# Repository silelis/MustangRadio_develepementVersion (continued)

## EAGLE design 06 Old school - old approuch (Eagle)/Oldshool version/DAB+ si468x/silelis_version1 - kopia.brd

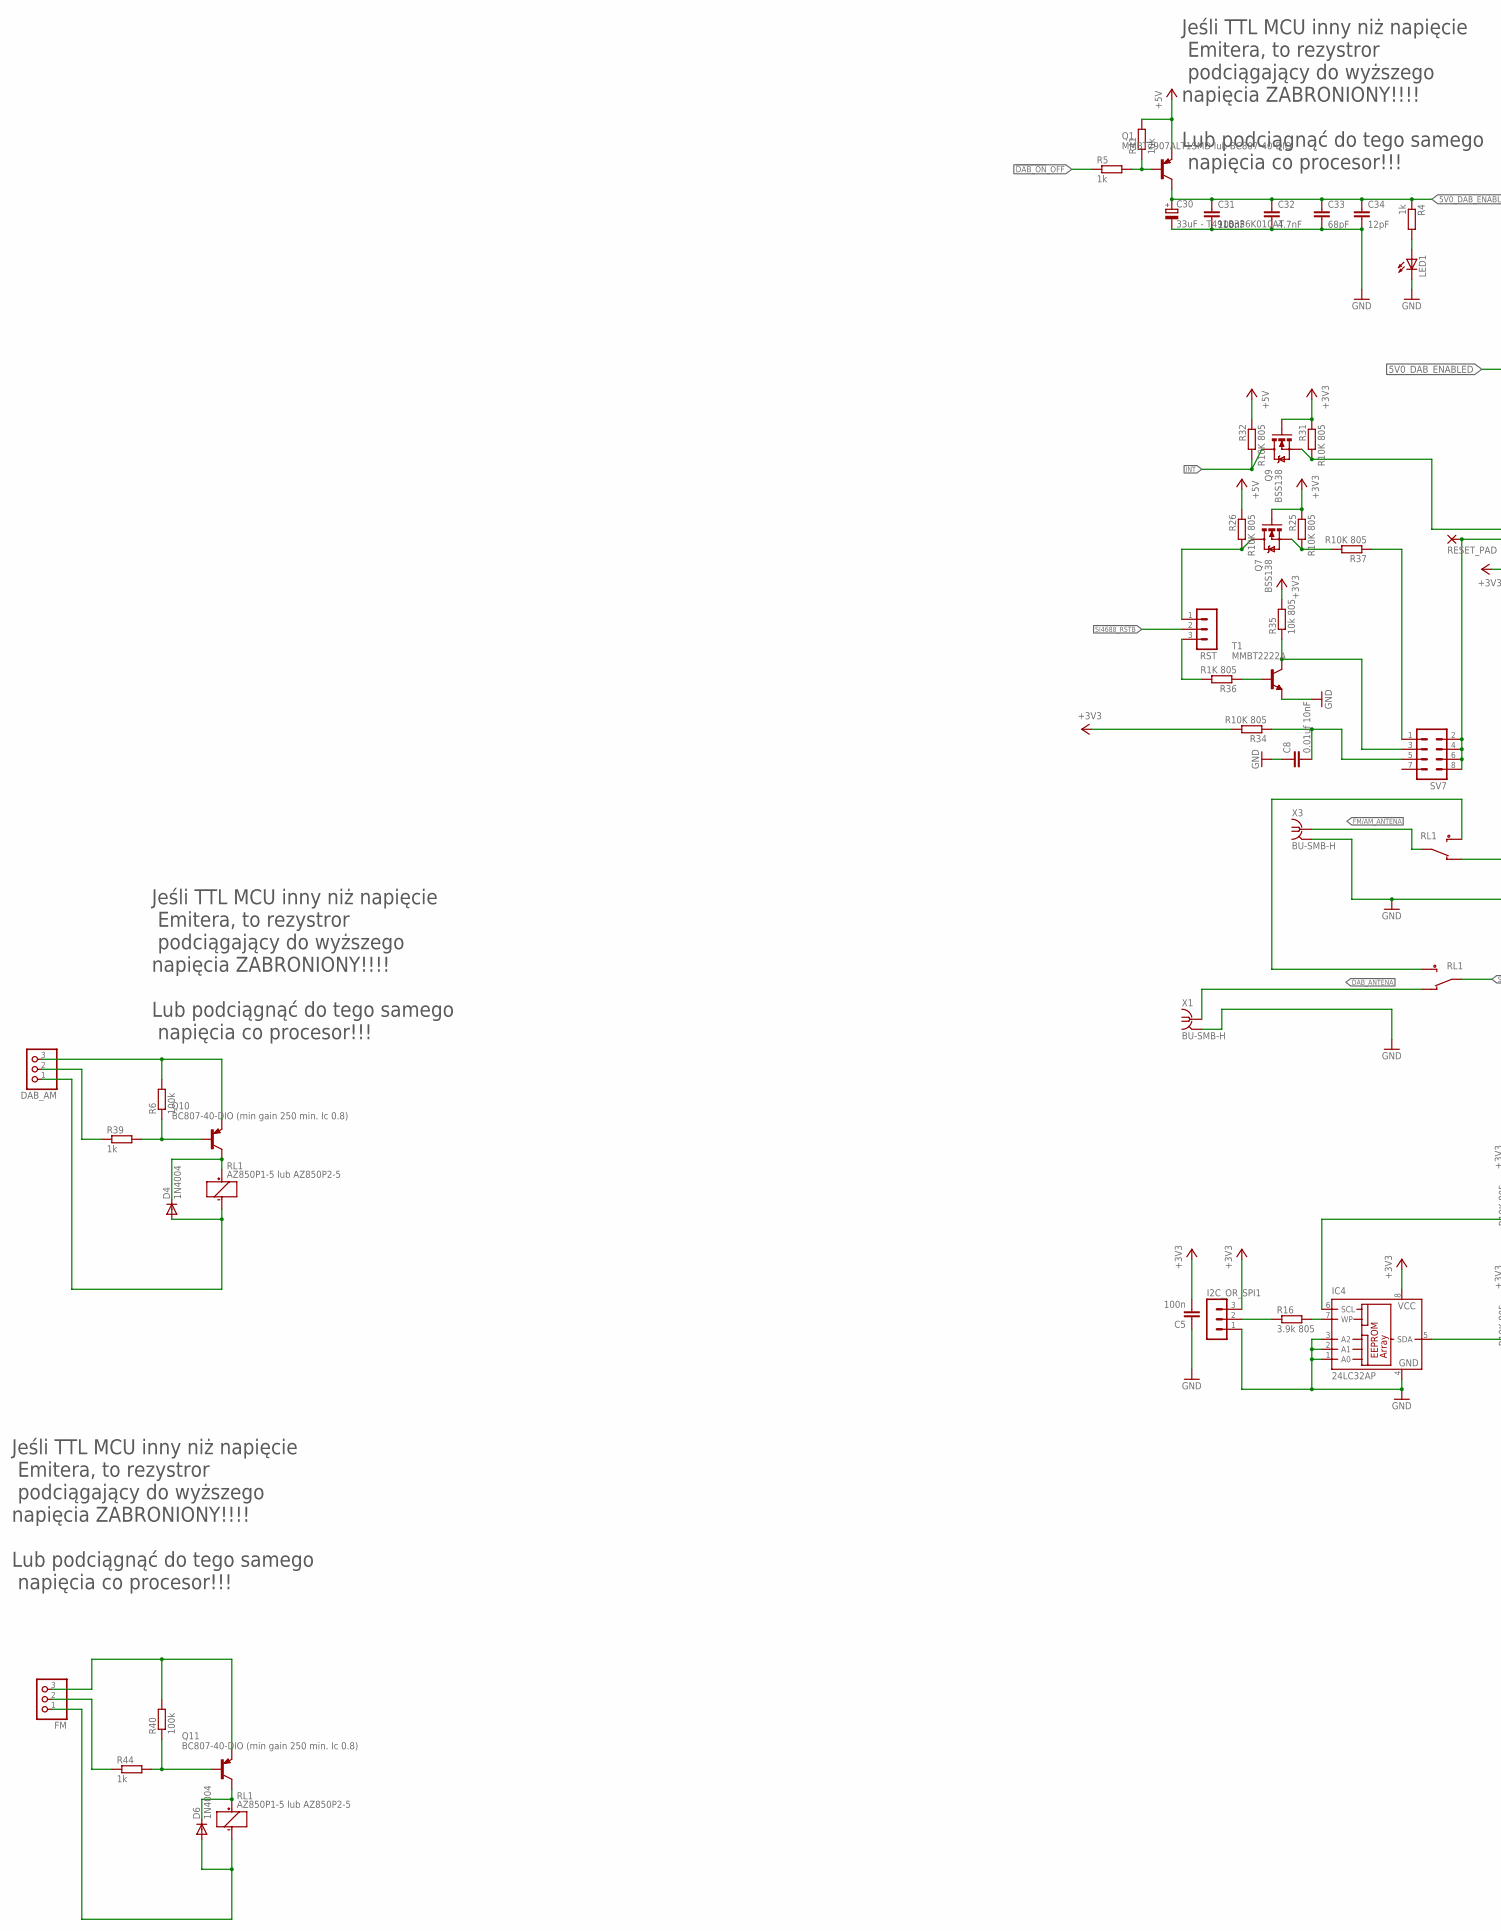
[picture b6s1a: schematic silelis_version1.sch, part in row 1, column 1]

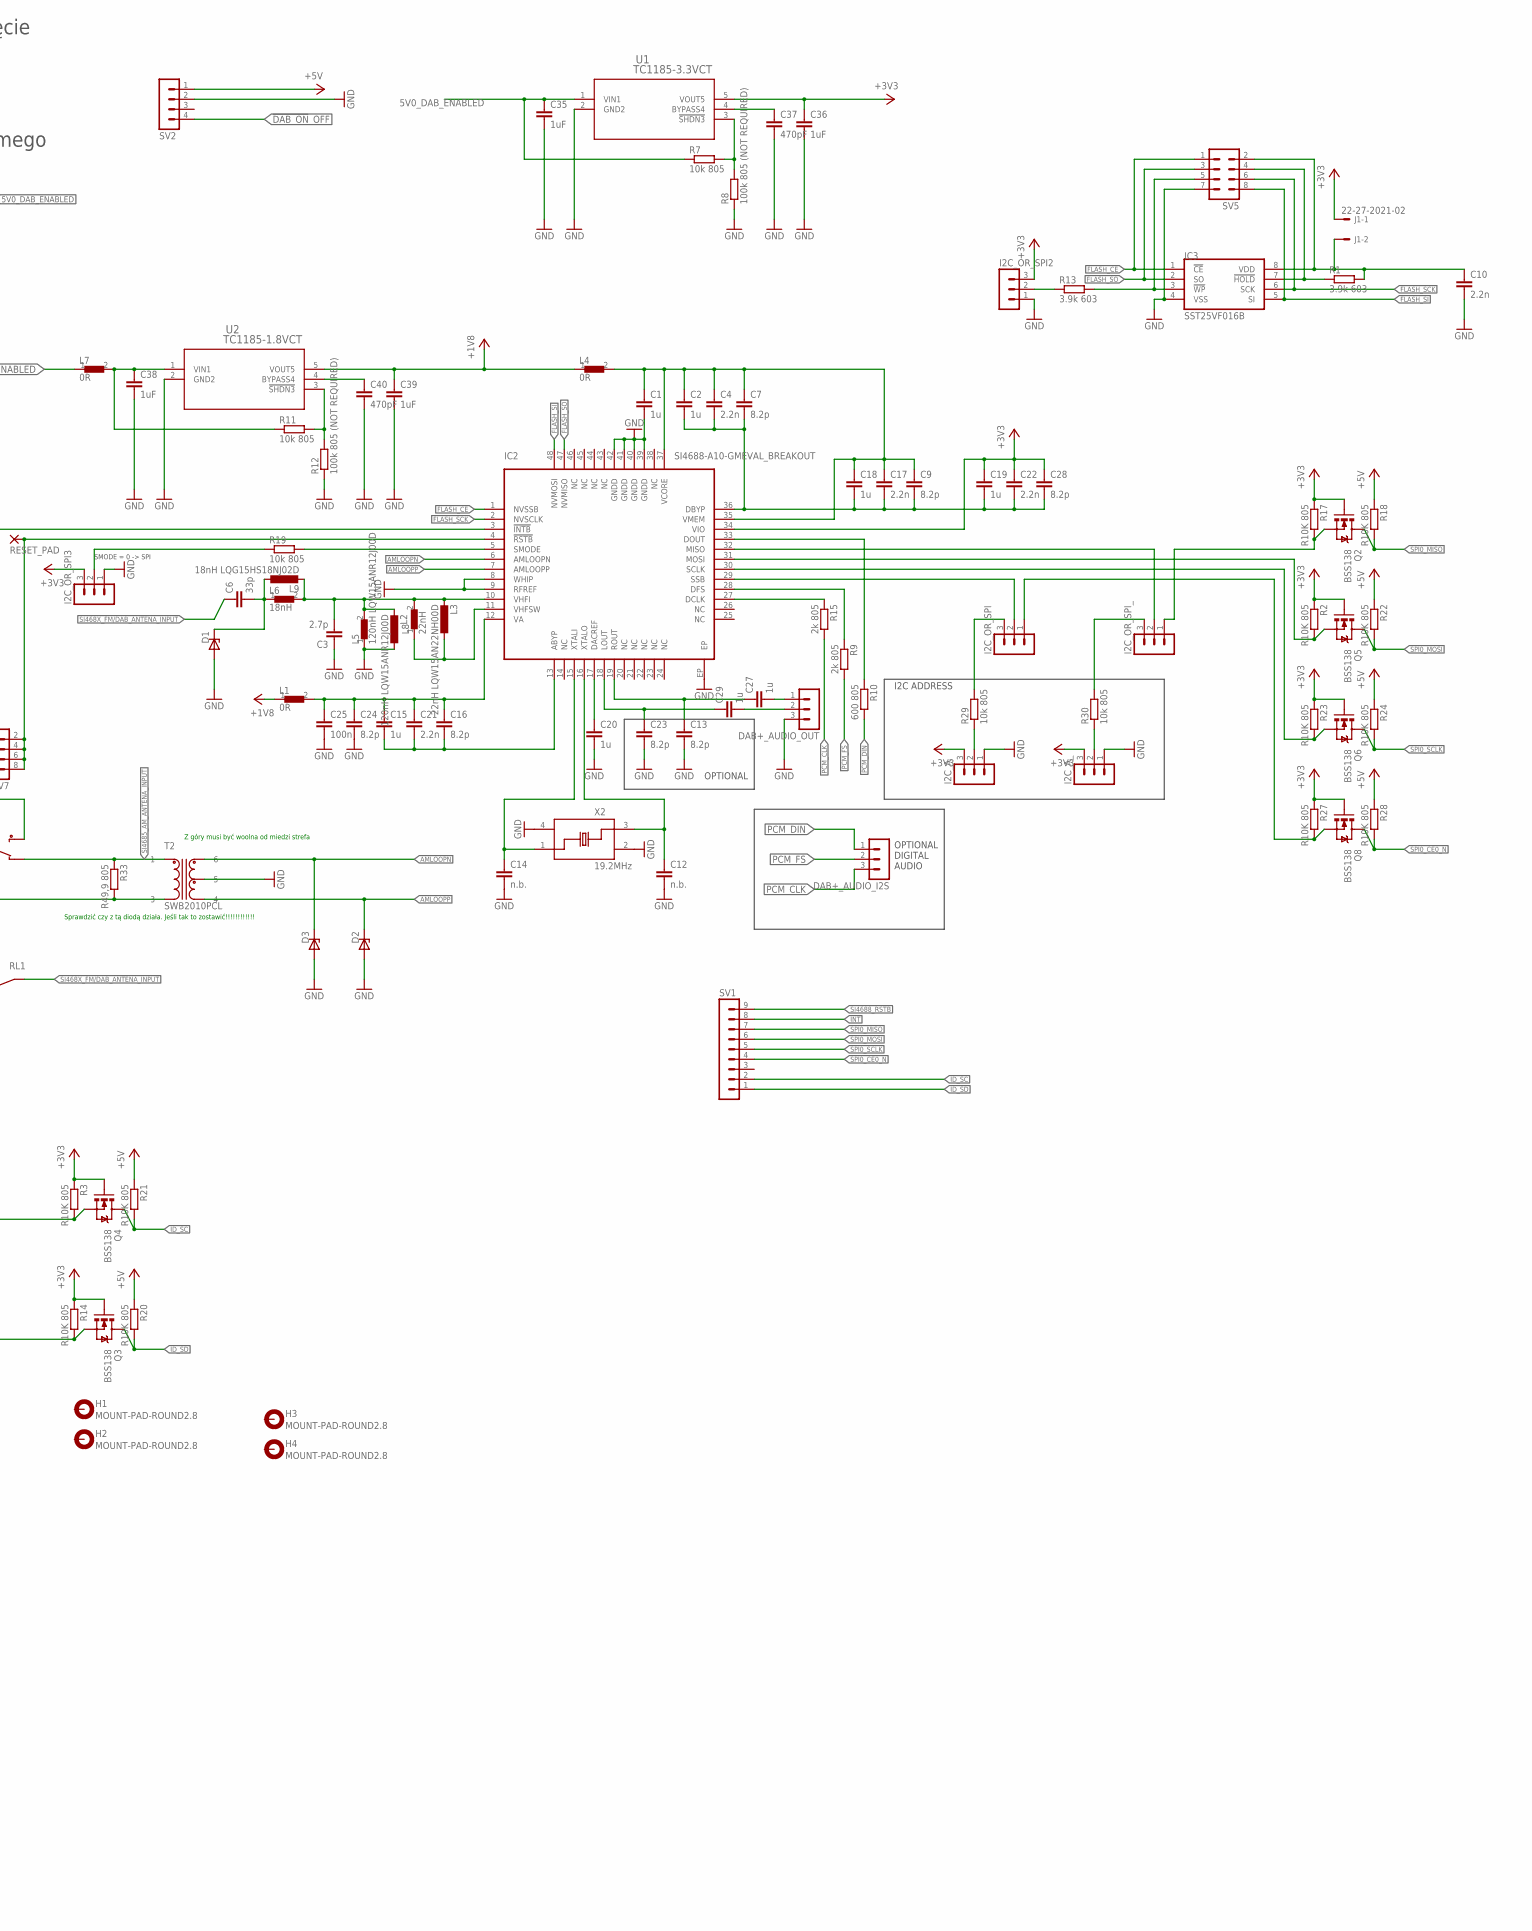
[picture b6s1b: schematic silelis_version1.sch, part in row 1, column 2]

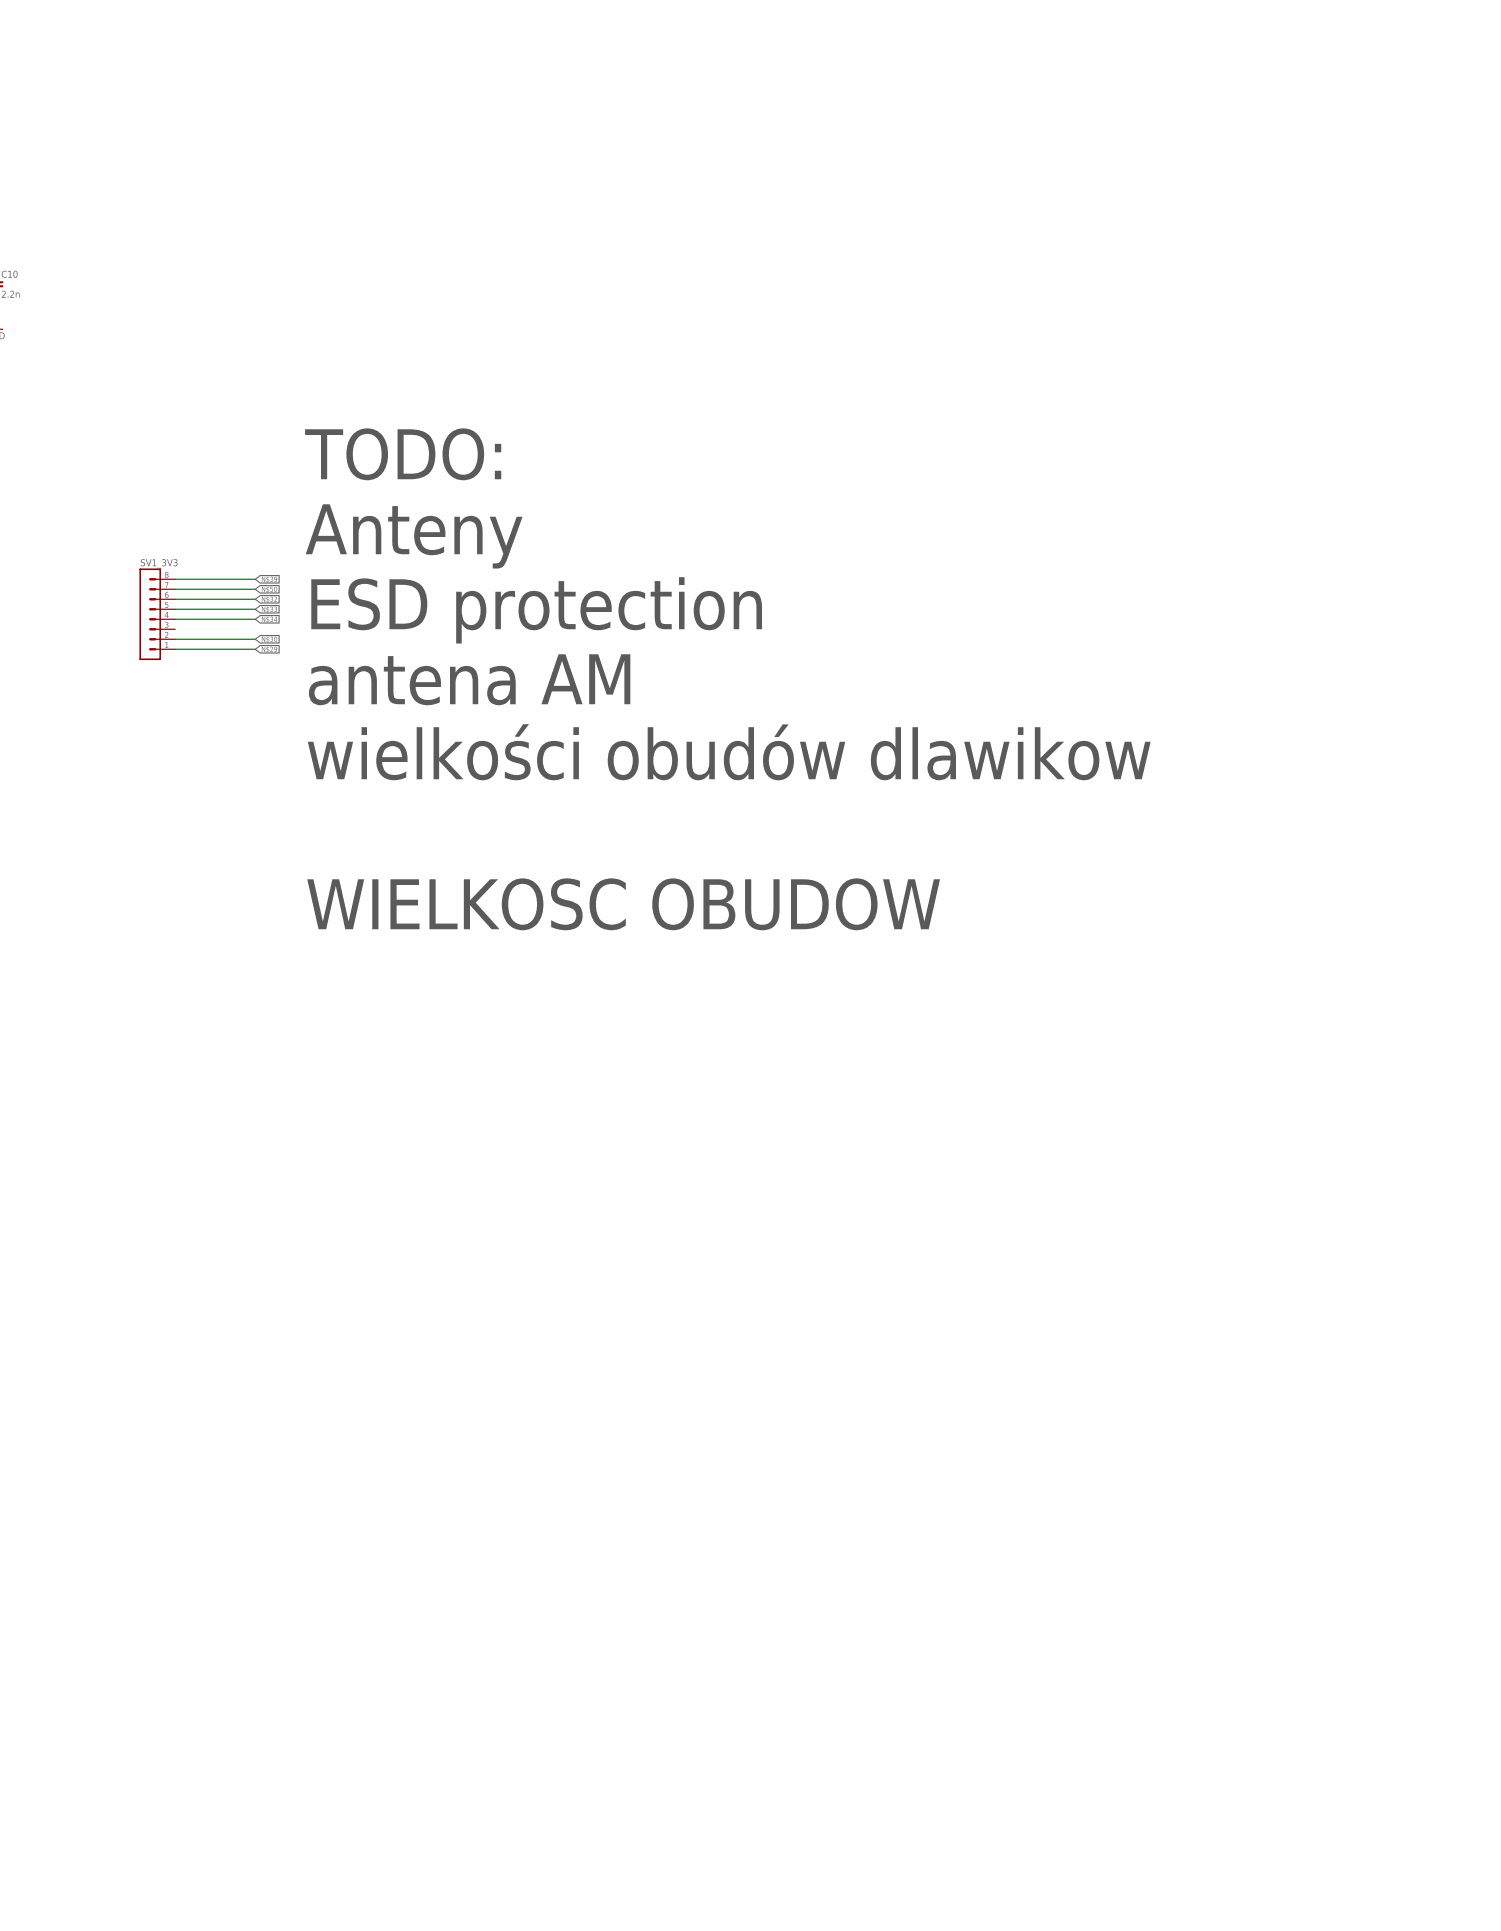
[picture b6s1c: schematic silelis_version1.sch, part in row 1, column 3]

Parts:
C1, C2, C15, C18, C19, C20, C27, C29: 1u; C0805
C3: 2.7p; C0603
C4, C10, C17, C21, C22: 2.2n; C0805
C5, C25: 100n; C0805
C6: 33p; C0603
C7, C9, C13, C16, C23, C24, C28: 8.2p; C0805
C8: 0.01uf 10nF; C0805
C12, C14: n.b.; C0805
C30: 33uF - T491B336K010AT; SMC_B; PARTNUM TAJB336K010R
C31: 100nF; C0805
C32: 4.7nF; C0805
C33: 68pF; C0805
C34: 12pF; C0603K
C35, C36, C38, C39: 1uF; C0805
C37, C40: 470pF; C0805
D1, D2, D3: ESD9L5.0; SOD923
D4, D6: 1N4004; DO41-10
DAB+_AUDIO_I2S: MA03-1
DAB+_AUDIO_OUT: MA03-1
DAB_AM: PINHD-1X03_2.54-SMD; 1X03SMD
FM: PINHD-1X03_2.54-SMD; 1X03SMD
H1, H2, H3, H4: MOUNT-PAD-ROUND2.8; 2,8-PAD
I2C_A, I2C_A_, I2C_OR_SPI, I2C_OR_SPI1, I2C_OR_SPI2, I2C_OR_SPI3, I2C_OR_SPI_: MA03-1
IC2: SI4688-A10-GMEVAL_BREAKOUT; QFN48-BREAKOUT
IC3: SST25VF016B; SOIC-8
IC4: 24LC32AP; DIL8
J1: 22-27-2021-02; 6410-02
L1, L4, L7: 0R; R0805
L2: 120nH LQW15ANR12J00D; SMD0402
L3: 22nH LQW15AN22NH00D; SMD0402
L5: 120nH LQW15ANR12J00D; R0805
L6: 18nH; R0805
L8: 22nH; R0805
L9: 18nH LQG15HS18NJ02D; SMD0402
LED1: LED3MM
Q1: MMBT2907ALT1SMD lub BC807-40-DIO; SOT23-BEC
Q2, Q3, Q4, Q5, Q6, Q7, Q8, Q9: BSS138; SOT23-3
Q10, Q11: BC807-40-DIO (min gain 250 min. Ic 0.8); SOT23-BEC
R1, R13: 3.9k 603; R0603
R2, R3, R14, R17, R18, R20, R21, R22, R23, R24, R25, R26, R27, R28, R31, R32, R34, R37: R10K 805; R0805
R4, R5, R39, R44: 1k; M0805
R6, R40: 100k; M0805
R7, R11, R19, R29, R30, R35: 10k 805; M0805
R8, R12: 100k 805 (NOT REQUIRED); M0805
R9, R15: 2k 805; M0805
R10: 600 805; M0805
R16: 3.9k 805; R0805
R33: R49,9 805; R0805
R36: R1K 805; R0805
R41: 10k; M0805
RESET_PAD: SMD2; SMD1,27-2,54
RL1: AZ850P1-5 lub AZ850P2-5; AZ850-2C
RST: MA03-1
SV1: MA09-1
SV1_3V3: MA08-1
SV2: MA04-1
SV5, SV7: MA04-2
T1: MMBT2222A; SOT23-BEC
T2: SWB2010PCL; COILCRAFT-SWBXXXX-PCL
U1: TC1185-3.3VCT; SOT-23-5_MC-M
U2: TC1185-1.8VCT; SOT-23-5_MC-M
X1, X3: BU-SMB-H
X2: 19.2MHz; XTAL_3.2X2.5

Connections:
5V0_DAB_ENABLED: C30.+, C31.1, C32.1, C33.1, C34.1, C35.1, L7.1, Q1.C, R4.1, R7.1, U1.1 (VIN1)
!DAB_ON!_OFF: R5.1, SV2.4
+1V8: C39.1, L1.1, L4.1, U2.5 (VOUT5)
+3V3: C5.2, C19.1, C22.1, C28.1, C36.1, I2C_A.3, I2C_A_.3, I2C_OR_SPI1.3, I2C_OR_SPI2.3, I2C_OR_SPI3.3, IC2.34 (VIO), IC4.8 (VCC), J1.1, Q2.1 (G), Q3.1 (G), Q4.1 (G), Q5.1 (G), Q6.1 (G), Q7.1 (G), Q8.1 (G), Q9.1 (G), R2.1, R3.1, R14.1, R17.1, R23.1, R25.1, R27.1, R31.1, R34.2, R35.2, U1.5 (VOUT5)
+5V: Q1.E, R18.1, R20.1, R21.1, R22.1, R24.1, R26.1, R28.1, R32.1, R41.2, SV2.1
AMLOOPN: D3.K (C), IC2.6 (AMLOOPN), T2.P$6 (6)
AMLOOPP: D2.K (C), IC2.7 (AMLOOPP), T2.P$4 (4)
DAB/AM_POSITION: DAB_AM.2, R39.1; also elsewhere on the board
DAB_ANTENA: RL1.P$9 (4), X1.1
FLASH_CE: IC2.1 (NVSSB), IC3.1 (!CE), SV5.1
FLASH_SCK: IC2.2 (NVSCLK), IC3.6 (SCK), SV5.6
FLASH_SI: IC2.48 (NVMOSI), IC3.5 (SI), SV5.8
FLASH_SO: IC2.47 (NVMISO), IC3.2 (SO), SV5.3
FM/AM_ANTENA: RL1.P$3 (5), X3.1
FM/AM_ANTENA_TO_SI468X_FM/DAB_ANTENA_INPUT: RL1.P$4 (6), RL1.P$7 (6)
FM_POSITION: FM.2, R44.1; also elsewhere on the board
GND: C1.2, C3.1, C5.1, C8.1, C10.2, C12.2, C13.2, C14.2, C20.2, C23.2, C24.2, C25.2, C30.-, C31.2, C32.2, C33.2, C34.2, C35.2, C36.2, C37.2, C38.2, C39.2, C40.2, D1.A, D2.A, D3.A, DAB+_AUDIO_OUT.3, I2C_A.1, I2C_A_.1, I2C_OR_SPI1.1, I2C_OR_SPI2.1, I2C_OR_SPI3.1, IC2.8 (WHIP), IC2.9 (RFREF), IC2.39 (GNDD), IC2.40 (GNDD), IC2.41 (GNDD), IC2.42 (GNDD), IC2.EP, IC3.4 (VSS), IC4.1 (A0), IC4.2 (A1), IC4.3 (A2), IC4.4 (GND), L2.1, L5.1, LED1.K (C), R8.1, R12.1, R33.2, SV2.2, SV5.7, T1.E, T2.P$3 (3), T2.P$5 (5), U1.2 (GND2), U2.2 (GND2), X1.2, X1.3 (2), X1.4 (2), X1.5 (2), X2.2 (GND), X2.4 (GND), X3.2, X3.3 (2), X3.4 (2), X3.5 (2)
ID_SC: Q4.3 (D), R21.2, SV1.2
ID_SD: Q3.3 (D), R20.2, SV1.1
INT: Q9.3 (D), R32.2, SV1.8
unnamed: C3.2, IC2.10 (VHFI), L2.2, L3.2, L5.2, L6.2, L8.2, L9.2
unnamed: IC2.11 (VHFSW), L3.1, L8.1
unnamed: C15.2, C16.2, C21.2, IC2.13 (ABYP)
unnamed: C2.2, C4.2, C7.2, C9.2, C17.2, C18.2, C19.2, C22.2, C28.2, IC2.36 (DBYP)
unnamed: C14.1, IC2.15 (XTALI), X2.1
unnamed: C12.1, IC2.16 (XTALO), X2.3
unnamed: C20.1, IC2.17 (DACREF)
unnamed: IC2.4 (!RSTB!), RESET_PAD.1, SV7.2, SV7.4, SV7.6, SV7.8
unnamed: I2C_OR_SPI2.2, R13.1
unnamed: C38.1, L7.2, R11.1, U2.1 (VIN1)
unnamed: C15.1, C16.1, C21.1, C24.1, C25.1, IC2.12 (VA), L1.2
unnamed 31: D4.A, DAB_AM.1, RL1.P$5 (-); also elsewhere on the board
unnamed: C1.1, C2.1, C4.1, C7.1, C9.1, C17.1, C18.1, IC2.35 (VMEM), IC2.37 (VCORE), L4.2
unnamed: IC2.28 (DFS), R9.1
unnamed: IC2.33 (DOUT), R10.1
unnamed: IC4.7 (WP), R16.2
unnamed: LED1.A, R4.2
unnamed: Q1.B, R5.2, R41.1
unnamed: C37.1, U1.4 (BYPASS4)
unnamed: R7.2, R8.2, U1.3 (!SHDN3)
unnamed: IC3.7 (!HOLD), R1.1, SV5.4
unnamed: IC2.27 (DCLK), R15.1
unnamed: C40.1, U2.4 (BYPASS4)
unnamed: R11.2, R12.2, U2.3 (!SHDN3)
unnamed: I2C_OR_SPI3.2, R19.1
unnamed: IC2.5 (SMODE), R19.2
unnamed: I2C_OR_SPI1.2, R16.1
unnamed: IC4.5 (SDA), Q3.2 (S), R14.2, SV1_3V3.1
unnamed: IC4.6 (SCL), Q4.2 (S), R3.2, SV1_3V3.2
unnamed: I2C_OR_SPI_.2, IC2.32 (MISO)
unnamed: IC2.31 (MOSI), Q5.2 (S), R2.2, SV1_3V3.6
unnamed: IC2.30 (SCLK), Q6.2 (S), R23.2, SV1_3V3.5
unnamed: I2C_OR_SPI.1, Q8.2 (S), R27.2, SV1_3V3.4
unnamed: I2C_A.2, R29.1
unnamed: I2C_A_.2, R30.1
unnamed: I2C_OR_SPI.3, R29.2
unnamed: I2C_OR_SPI_.3, R30.2
unnamed: IC2.3 (!INTB!), Q9.2 (S), R31.2, SV1_3V3.8
unnamed: R35.1, SV7.3, T1.C
unnamed: C10.1, IC3.8 (VDD), J1.2, R1.2, SV5.2
unnamed: IC3.3 (!WP), R13.2, SV5.5
unnamed: C27.2, DAB+_AUDIO_OUT.1
unnamed: C29.2, DAB+_AUDIO_OUT.2
unnamed: I2C_OR_SPI.2, IC2.29 (SSB)
unnamed: I2C_OR_SPI_.1, Q2.2 (S), R17.2, SV1_3V3.7
unnamed: R36.2, RST.3
unnamed: C8.2, R34.1, SV7.5
unnamed: R36.1, T1.B
unnamed: Q7.2 (S), R25.2, R37.2
unnamed: Q7.3 (D), R26.2, RST.1
unnamed: R37.1, SV7.1
unnamed: Q10.B, R6.1, R39.2
unnamed 72: DAB_AM.3, Q10.E, R6.2; also elsewhere on the board
unnamed: D4.C, Q10.C, RL1.P$1 (+)
unnamed: Q11.B, R40.1, R44.2
unnamed 75: FM.3, Q11.E, R40.2; also elsewhere on the board
unnamed 76: D6.A, FM.1, RL1.P$6 (-); also elsewhere on the board
unnamed: D6.C, Q11.C, RL1.P$10 (+)
PCM_CLK: DAB+_AUDIO_I2S.3, R15.2
PCM_DIN: DAB+_AUDIO_I2S.1, R10.2
PCM_FS: DAB+_AUDIO_I2S.2, R9.2
SI4685_AM_ANTENA_INPUT: R33.1, RL1.P$2 (4), T2.P$1 (1)
SI4688_LOUT: C23.1, C29.1, IC2.18 (LOUT)
SI4688_ROUT: C13.1, C27.1, IC2.19 (ROUT)
SI4688_RSTB: RST.2, SV1.9
SPI0_CE0_N: Q8.3 (D), R28.2, SV1.4
SPI0_MISO: Q2.3 (D), R18.2, SV1.7
SPI0_MOSI: Q5.3 (D), R22.2, SV1.6
SPI0_SCLK: Q6.3 (D), R24.2, SV1.5

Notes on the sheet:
SMODE = 0 -> SPI
OPTIONAL DIGITAL AUDIO
TODO: Anteny ESD protection antena AM wielkości obudów dlawikow WIELKOSC OBUDOW
I2C ADDRESS
OPTIONAL
Jeśli TTL MCU inny niż napięcie Emitera, to rezystror podciągający do wyższego napięcia ZABRONIONY!!!! Lub podciągnąć do tego samego napięcia co procesor!!!
Sprawdzić czy z tą diodą działa. Jeśli tak to zostawić!!!!!!!!!!!!
Z góry musi być woolna od miedzi strefa

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
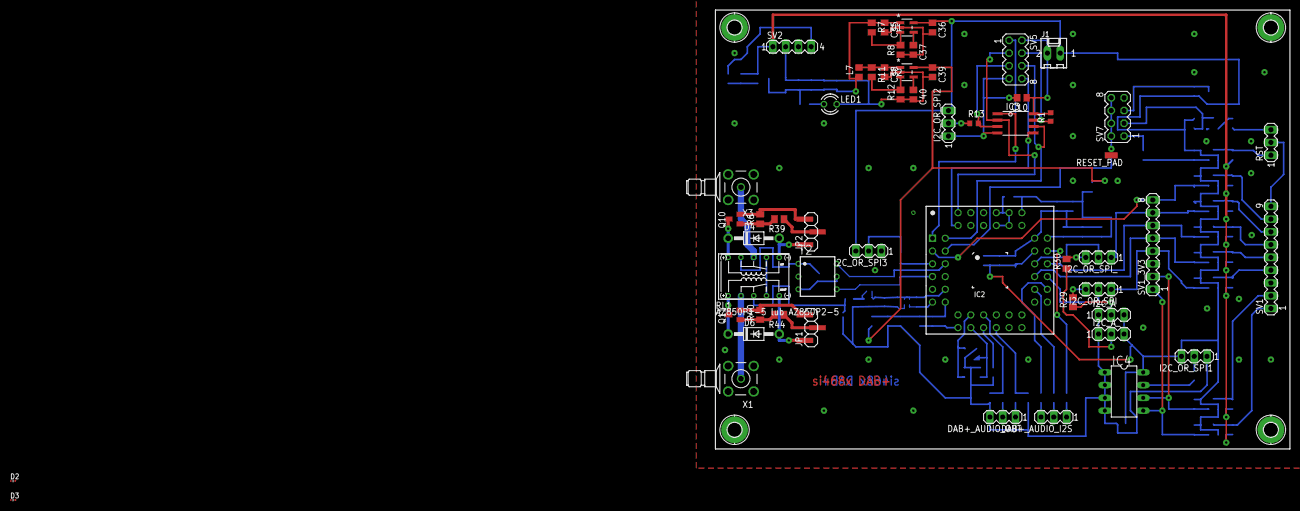
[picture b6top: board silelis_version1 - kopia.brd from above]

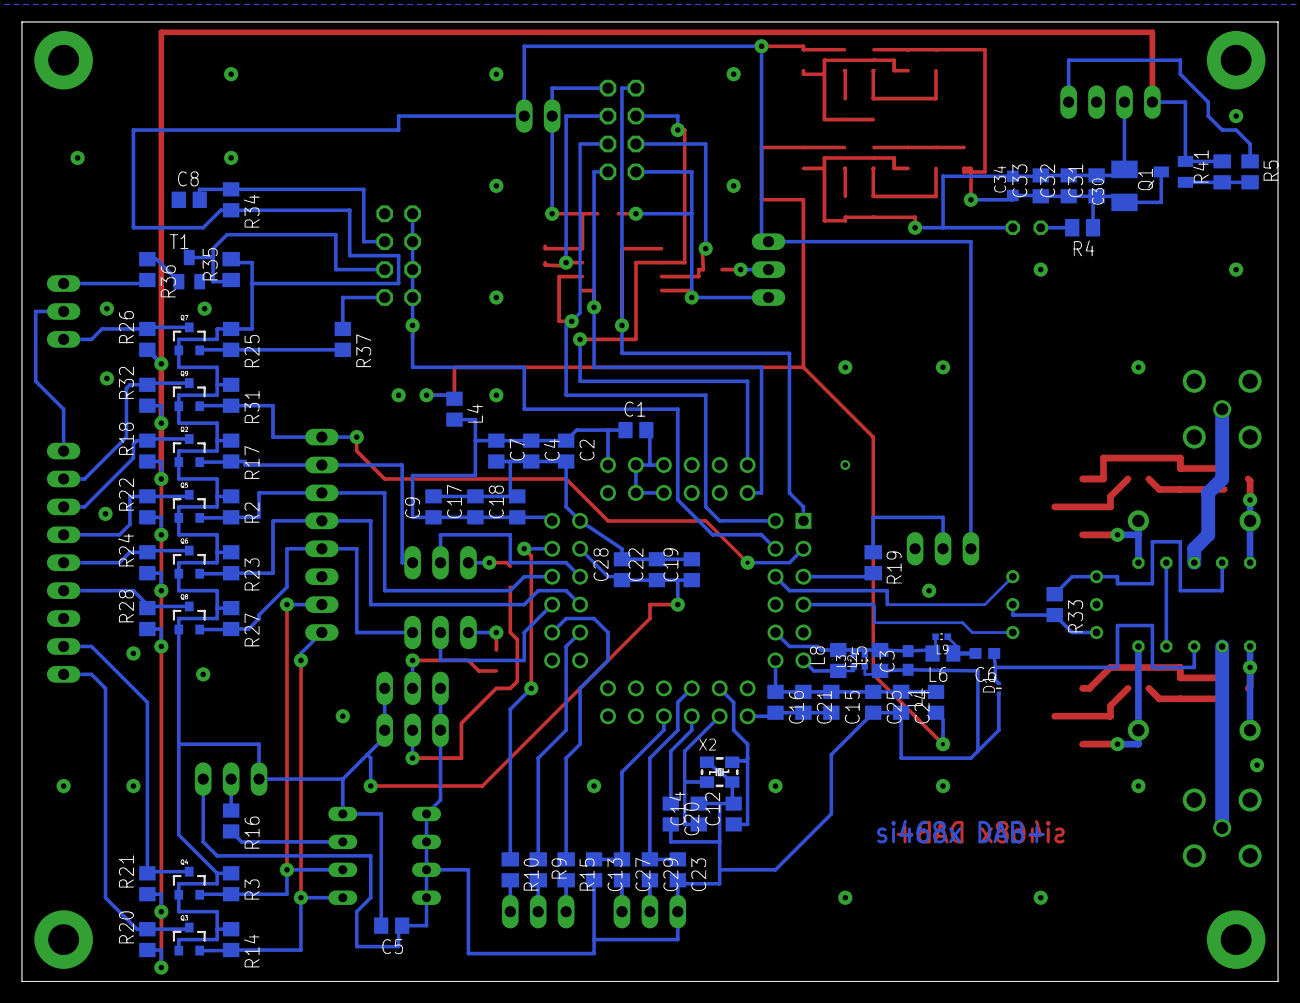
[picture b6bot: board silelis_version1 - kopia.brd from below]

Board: 2 copper layers, 114.3 x 87.3 mm, 139 parts (80 on the bottom side), 91 nets.

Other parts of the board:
JP1, JP2: 1X03SMD

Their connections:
DAB/AM_POSITION: JP2.2; also elsewhere on the board
FM_POSITION: JP1.2; also elsewhere on the board
unnamed 31: JP2.1; also elsewhere on the board
unnamed 72: JP2.3; also elsewhere on the board
unnamed 75: JP1.3; also elsewhere on the board
unnamed 76: JP1.1; also elsewhere on the board

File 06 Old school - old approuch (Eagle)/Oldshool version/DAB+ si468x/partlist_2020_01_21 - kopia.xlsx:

Partl | ist
Expor | ted | from silelis_version1.sch at 21.01.2020 11:50
EAGLE | Ve | rsion 7.6.0 Copyright (c) 1988-2016 CadSoft
Assem | bly | variant:
Part |  | Value | ilość | Device | Package | Library | Sheet
 |  |  |  |  |  |  |  |  | Mouser |  | TME
 |  |  |  |  |  |  |  |  | Cena | link | Cena | Link
IC2 |  | SI4688-A10-GMEVAL_BREAKOUT |  | SI4688-A10-GMEVAL_B | REAKOUT QFN48-BREAKOUT | SI4688-A10- | GM 1 |  | 60.17 | SI4689-A10-GM
IC3 |  | SST25VF016B |  | SST25VF016B | SOIC-8 | sst25 | 1 |  | 5.58 | SST25VF016B-50-4I-S2AF | 5.16 | SST25VF016B-50-4I-S2AF
T2 |  | SWB2010PCL |  | SWB2010PCL | COILCRAFT-SWBXXXX-PCL | CoilCraft | 1 |  | 13.12 | SWB2010PCL
U2 |  | TC1185-1.8VCT |  | TC1185-X.XXCT713SOT | -23-5_MC-M SOT-23-5_MC-M | TC1185 | 1 |  | 1.45 | TC1185-1.8VCT | 1.3466 | TC1185-1.8VCT
U1 |  | TC1185-3.3VCT |  | TC1185-X.XXCT713SOT | -23-5_MC-M SOT-23-5_MC-M | TC1185 | 1 |  | 1.45 | TC1185-3.3VCT | 1.4467000000000001 | TC1185-3.3VCT
X1-DA | B_A | NT SMA_LP_1.57MM |  | SMA_LP_1.57MM | SMA_LP_1.57MM | con_sma | 1 |  |  |  | 11.89 | SMB1252B13G50
 |  |  |  |  |  |  |  |  |  |  | 50.53 | A00030 | SMB1252B13G50 lub | antena: | A00030
 |  |  |  |  |  |  |  |  |  |  | 3.66 | ZRS-AA-4
X2-FM | _AM | _ANT |  | MTA02-156 | 1X2MTA | con-amp | 1 |  | 9.94 | Amphenol RF2FA1-NCRP-PCB-6 / MOLEX 73403-5112 / DELOCK 89773 FAKRA B |  | Amphenol RF2FA1-NCRP-PCB-6 / MOLEX 73403-5112 / DELOCK 89773 FAKRA B
 |  |  |  |  |  |  |  |  |  |  | 8.9600000000000009 | ZRS-FAKRA-DIN
 |  |  |  |  |  |  |  |  |  |  |  |  | CAR-GNANT lub CAR-006 lub (ZRS-AA-4 + Amphenol RF2FA1-NCRP-PCB-6 / MOLEX 73403-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
IC4 |  | 24LC32AP |  | 24LC32AP | DIL8 | microchip | 1 | czy nie potrzebny większy |  |  |  |  | 24LC512-I/P
RL1 |  | AZ850P2-5 | 1 | AZ850P2-5 | AZ850-2C | relay_silel | is 1 |  | 13.25 | 769-TQ2-5V | 12.01 | AZ850P2-5
X2 |  | 19.2MHz |  | XTAL_3.2X2.5 | XTAL_3.2X2.5 | generisch | 1 |  | 4.08 | ABM8-19.200MHZ-10-1-U-T | 9.5225600000000004 | I747-2P3-19.2000M (OSTATECZNIE??) | ABM8-19.200MHZ-10-1-U-T
R6 |  | 100k | 4 | R-EU_M0805 | M0805 | rcl | 1
L1 |  | 0R | 3 | FERRITR0805 | R0805 | ferrit_bear | 1 | mam 1R
R7 |  | 10k 805 | 25 | R-EU_M0805 | M0805 | rcl | 1
R4 |  | 1k | 5 | R-EU_M0805 | M0805 | rcl | 1
R9 |  | 2k 805 | 5 | R-EU_M0805 | M0805 | rcl | 1
R1 |  | 3.9k 805 | 3 | R-EU_M0805 | M0805 | rcl | 1 | mam 3.9k 1206 | 0.51 | 279-CPF0603B3K9E1 | 0.35199999999999998 | ERA3AEB392V
R44 |  | 4.7k | 1 | R-EU_M0805 | M0805 | rcl | 1
R10 |  | 600805 |  | R-EU_M0805 | M0805 | rcl | 1 | mam 680
D4 |  | 1N4004 |  | 1N4004 | DO41-10 | adafruit | 1
D6 |  | 1N4004 |  | 1N4004 | DO41-10 | adafruit | 1
L5 |  | 120nH |  | FERRITR0805 | R0805 | ferrit_bear | 1 |  | 0.70599999999999996 | LQW15ANR12J00D | 0.52447999999999995 | LQW18ANR12G00D | LQW15ANR12J00D | wziąć też jakieś 604
L6 |  | 18nH |  | FERRITR0805 | R0805 | ferrit_bear | 1 |  | 0.39200000000000002 | LQG15HS18NJ02D | 0.39484000000000002 | LQG18HN18NJ00D | LQG15HS18NJ02D | wziąć też jakieś 604
L8 |  | 22nH |  | FERRITR0805 | R0805 | ferrit_bear | 1 |  | 0.746 | LQW15AN22NH00D | 0.39493 | LQG18HN22NJ00D | LQW15AN22NH00D | wziąć też jakieś 604
C40 |  | 470pF | 2 | C-EUC0805 | C0805 | resistor | 1
C33 |  | 68pF | 1 | C-EUC0805 | C0805 | resistor | 1
C7 |  | 8.2p | 7 | C-EUC0805 | C0805 | resistor | 1
C6 |  | 33p |  | C-EUC0805 | C0805 | resistor | 1 |  | 0.23499999999999999 | 80-C0603C330K5HAUTO | 0.45008999999999999 | C0603C330J1GACTU
C3 |  | 2.7p |  | C-EUC0805 | C0805 | resistor | 1 |  | 0.39200000000000002 | 603-C0603CRNPO9BN2R7 (za 1) | 8.2369999999999999E-2 | CL10C2R7CB8NNNC (za 100)
C34 |  | 12pF |  | C-EUC0603K | C0603K | resistor | 1
C4 |  | 2.2n | 5 | C-EUC0805 | C0805 | resistor | 1
C8 |  | 0.01uf 10n |  | C-EUC0805 | C0805 | rcl | 1
C32 |  | 4.7nF | 1 | C-EUC0805 | C0805 | resistor | 1
C5 |  | 100n | 3 | C-EUC0805 | C0805 | resistor | 1
C1 |  | 1u | 12 | C-EUC0805 | C0805 | resistor | 1
C30 |  | 33uF - T491B336K010AT |  | CPOL-EUSMCB | SMC_B | resistor | 1
C12 |  | n.b. |  | C-EUC0805 | C0805 | resistor | 1
C14 |  | n.b. |  | C-EUC0805 | C0805 | resistor | 1
Q10 |  | BC807-40-DIO (min gain 250 min. Ic 0.8) | 2 | MMBT2907ALT1SMD | SOT23-BEC | transistor- | pnp 1 | PNP |  |  |  |  | MMBT5401
Q2 |  | BSS138 | 8 | MOSFET-NCHANNELSMD | SOT23-3 | SparkFun | 1 |  |  |  | 0.59450000000000003 | BSS138AKAR | 4 mam
D1 |  | ESD9L5.0 | 1 | ESD9L5.0 | SOD923 | generisch | 1 |  |  |  | 0.59450000000000003 | ESD9L5.0ST5G
T1 |  | MMBT2222A |  | MMBT918LT1-NPN-SOT2 | 3-BEC SOT23-BEC | transistor | 1
Q1 |  | MMBT2907ALT1SMD lub BC807-40-DIO |  | MMBT2907ALT1SMD | SOT23-BEC | transistor- | pnp 1
 |  | chinche |  | 2 komplety
 |  |  |  |  |  |  |  |  |  |  |  |  | tranzystory mam:
 |  |  |  |  |  |  |  |  |  |  |  |  | BCR555E6327 | 20
J1 |  | 22-27-2021-02 |  | 22-27-2021-02 | 6410-02 | con-molex | 1 |  |  |  |  |  | MMBTRC105SS-DIO
I2C_A |  |  |  | MA03-1 | MA03-1 | con-lstb | 1 |  |  |  |  |  | MBR0530T1G | 6
I2C_A | _ |  |  | MA03-1 | MA03-1 | con-lstb | 1 |  |  |  |  |  | AP7333-33SAG-7 | 4
I2C_O | R_S | PI |  | MA03-1 | MA03-1 | con-lstb | 1 |  |  |  |  |  | MBR0540 T 1G | 4
I2C_O | R_S | PI_ |  | MA03-1 | MA03-1 | con-lstb | 1
I2C_O | R_S | PI1 |  | MA03-1 | MA03-1 | con-lstb | 1
I2C_O | R_S | PI2 |  | MA03-1 | MA03-1 | con-lstb | 1
I2C_O | R_S | PI3 |  | MA03-1 | MA03-1 | con-lstb | 1
I2C_O | R_S | PI4 |  | MA03-1 | MA03-1 | con-lstb | 1
SV1 |  |  |  | MA09-1 | MA09-1 | con-lstb | 1 |  |  |  |  |  | W KiCAD używam
SV1_3 | V3 |  |  | MA08-1 | MA08-1 | con-lstb | 1 |  |  |  |  |  | BC817
SV2 |  |  |  | MA04-1 | MA04-1 | con-lstb | 1 |  |  |  |  |  | MMBT5401
SV5 |  |  |  | MA04-2 | MA04-2 | con-lstb | 1
SV7 |  |  |  | MA04-2 | MA04-2 | con-lstb | 1
JP1 |  |  |  | PINHD-1X03_2.54-SMD | 1X03SMD | pinhead-2 | 1
JP2 |  |  |  | PINHD-1X03_2.54-SMD | 1X03SMD | pinhead-2 | 1
DAB+_ | AUD | IO_I2S |  | MA03-1 | MA03-1 | con-lstb | 1
DAB+_ | AUD | IO_OUT |  | MA03-1 | MA03-1 | con-lstb | 1
LED1 |  |  |  | LED3MM | LED3MM | led | 1
